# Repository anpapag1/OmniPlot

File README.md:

# OmniPlot

OmniPlot is an ESP-based controller sketch for a 3-wheel omnidirectional plotting robot. The main sketch is `OmniPlot.ino` and it uses the AccelStepper and MultiStepper libraries to drive three stepper motors.

This repository also contains PCB/board files under the `OmniPlot-PCB/` folder.

## Quick summary

- Libraries to download: 
  - AccelStepper.h  `for steppers`
  - ESP32Servo.h  `for pen servo`
  - Adafruit_SSD1306.h `for display`

- Pinout:
  - Stepper1 (Back left) (`step = 35`, `dir  = 34`, `en  = 26`)
  - Stepper2 (front) (`step = 14`, `dir  = 12`, `en  = 27`)
  - Stepper3 (Back right) (`step = 25`, `dir  = 33`, `en  = 32`)
  - Pen_Servo (`servo_Pin = 23`)
  - Encoder (`A = 19`, `B = 18`, `btn = 5`)
  - Oled 
    - `SCREEN_WIDTH 128`
    - `SCREEN_HEIGHT 32`
    - `OLED_RESET -1 `
    - `SCREEN_ADDRESS 0x3C`

## Functions and behavior

This section documents the important functions in `OmniPlot.ino` and what each does.

- `GnR(int speed, int steps1, int steps2, int steps3)`
  - Sets `setMaxSpeed(speed)` for each stepper (units: steps per second for AccelStepper).
  - Writes the requested target positions into a `long gotoposition[3]` array.
  - Calls `steppersControl.moveTo(gotoposition);` followed by `steppersControl.runSpeedToPosition();` — this blocks until all steppers reach their target positions.
  - Waits 1 second, then commands all motors to return to position zero and waits again.

- `omniTest()`
  - A simple test routine that calls `GnR(...)` with several sets of speeds and step targets to demonstrate movement patterns. The calls look like:
    - `GnR(1000, 1000, -1000, 0);`
    - `GnR(2000, 0, 1000, -1000);`
    - and so on.
  - These sequences are examples — change or expand them to drive your robot.

- `spin(int steps)`
  - Example helper that sets all motors to a target (int steps) and back to zero. Also uses `runSpeedToPosition()` so it blocks until complete.

## Rotary Encoder with Interrupts

To read a rotary encoder efficiently using hardware interrupts on ESP32, use the following code pattern:

```cpp
// Encoder pin definitions
const int encoderPinA = 19;  // CLK
const int encoderPinB = 18;  // DT
const int encoderBtn = 5;    // SW (button)

volatile long encoderPosition = 0;
volatile bool buttonPressed = false;

// Interrupt service routine for encoder
void IRAM_ATTR encoderISR() {
  int stateB = digitalRead(encoderPinB);
  if (stateB == HIGH) {
    encoderPosition++;  // Clockwise
  } else {
    encoderPosition--;  // Counter-clockwise
  }
}

// Interrupt service routine for button
void IRAM_ATTR buttonISR() {
  buttonPressed = true;
}

void setup() {
  // Configure encoder pins
  pinMode(encoderPinA, INPUT_PULLUP);
  pinMode(encoderPinB, INPUT_PULLUP);
  pinMode(encoderBtn, INPUT_PULLUP);
  
  // Attach interrupts (trigger on FALLING edge)
  attachInterrupt(digitalPinToInterrupt(encoderPinA), encoderISR, FALLING);
  attachInterrupt(digitalPinToInterrupt(encoderBtn), buttonISR, FALLING);
}

void loop() {
  // Read encoder position (interrupt updates it automatically)
  static long lastPosition = 0;
  if (encoderPosition != lastPosition) {
    Serial.print("Encoder: ");
    Serial.println(encoderPosition);
    lastPosition = encoderPosition;
  }
  
  // Check button press
  if (buttonPressed) {
    Serial.println("Button pressed!");
    buttonPressed = false;  // Reset flag
    delay(200);  // Simple debounce
  }
}
```

**Key points:**
- Use `IRAM_ATTR` for interrupt functions to place them in RAM for faster execution
- Use `volatile` for variables shared between interrupts and main code
- GPIO 19 and 18 support interrupts and are safe for encoder use
- The encoder position updates automatically in the background via interrupts

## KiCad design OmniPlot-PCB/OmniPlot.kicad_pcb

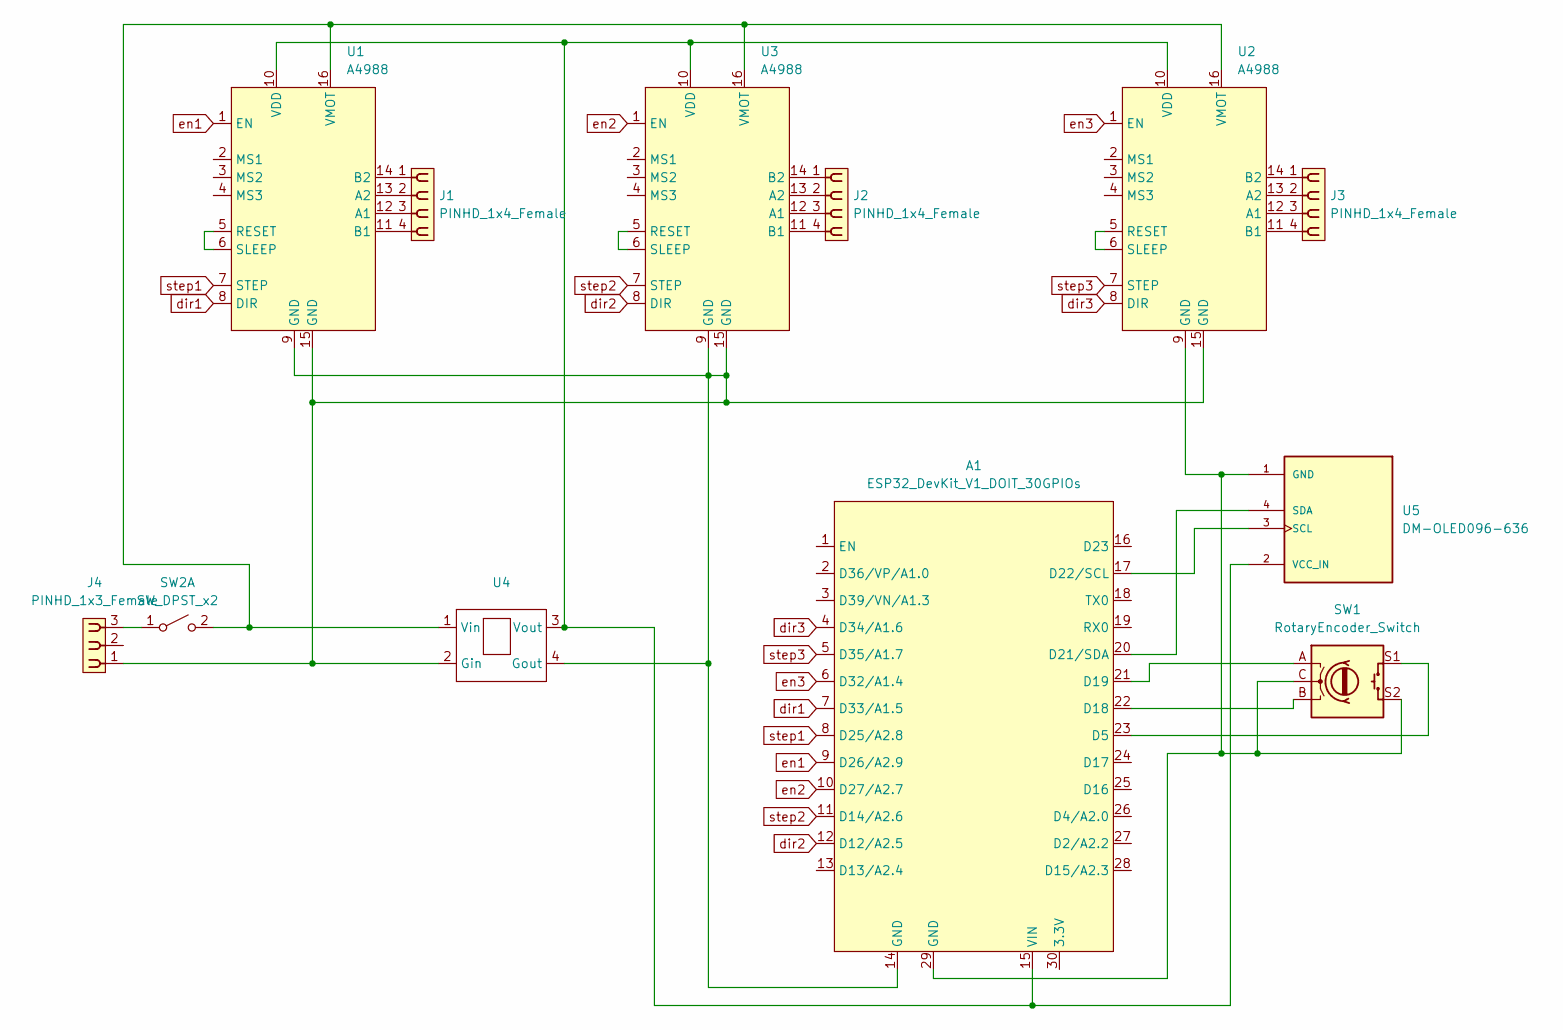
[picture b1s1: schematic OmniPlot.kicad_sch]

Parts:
A1: ESP32_DevKit_V1_DOIT_30GPIOs; DOIT_ESP32_DEVKIT_30Pins
J1, J2, J3: PINHD_1x4_Female; PinSocket_1x04_P2.54mm_Vertical
J4: PINHD_1x3_Female; PinSocket_1x03_P2.54mm_Vertical
SW1: RotaryEncoder_Switch; RotaryEncoder_Alps_EC11E-Switch_Vertical_H20mm
SW2: SW_DPST_x2; PinSocket_1x03_P2.54mm_Vertical
U1, U2, U3: A4988; A4988_Breakout
U4: 12v to 5v
U5: DM-OLED096-636; MODULE_DM-OLED096-636; PARTREV 2018-09-10

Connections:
unnamed: A1.23 (D5), SW1.S1
unnamed: A1.22 (D18), SW1.B
unnamed: A1.21 (D19), SW1.A
unnamed: A1.20 (D21/SDA), U5.4 (SDA)
unnamed: A1.17 (D22/SCL), U5.3 (SCL)
unnamed: A1.15 (VIN), U1.10 (VDD), U2.10 (VDD), U3.10 (VDD), U4.3 (Vout), U5.2 (VCC_IN)
unnamed: J4.3, SW2.1 (A)
unnamed: SW2.2 (B), U1.16 (VMOT), U2.16 (VMOT), U3.16 (VMOT), U4.1 (Vin)
unnamed: J1.3, U1.12 (A1)
unnamed: J1.2, U1.13 (A2)
unnamed: J1.4, U1.11 (B1)
unnamed: J1.1, U1.14 (B2)
unnamed: U1.5 (RESET), U1.6 (SLEEP)
unnamed: J3.3, U2.12 (A1)
unnamed: J3.2, U2.13 (A2)
unnamed: J3.4, U2.11 (B1)
unnamed: J3.1, U2.14 (B2)
unnamed: U2.5 (RESET), U2.6 (SLEEP)
unnamed: J2.3, U3.12 (A1)
unnamed: J2.2, U3.13 (A2)
unnamed: J2.4, U3.11 (B1)
unnamed: J2.1, U3.14 (B2)
unnamed: U3.5 (RESET), U3.6 (SLEEP)
unnamed: A1.14 (GND), J4.1, U1.9 (GND), U1.15 (GND), U2.15 (GND), U3.9 (GND), U3.15 (GND), U4.2 (Gin), U4.4 (Gout)
unnamed: A1.29 (GND), SW1.C, SW1.S2, U2.9 (GND), U5.1 (GND)
dir1: A1.7 (D33/A1.5), U1.8 (DIR)
dir2: A1.12 (D12/A2.5), U3.8 (DIR)
dir3: A1.4 (D34/A1.6), U2.8 (DIR)
en1: A1.9 (D26/A2.9), U1.1 (EN)
en2: A1.10 (D27/A2.7), U3.1 (EN)
en3: A1.6 (D32/A1.4), U2.1 (EN)
step1: A1.8 (D25/A2.8), U1.7 (STEP)
step2: A1.11 (D14/A2.6), U3.7 (STEP)
step3: A1.5 (D35/A1.7), U2.7 (STEP)

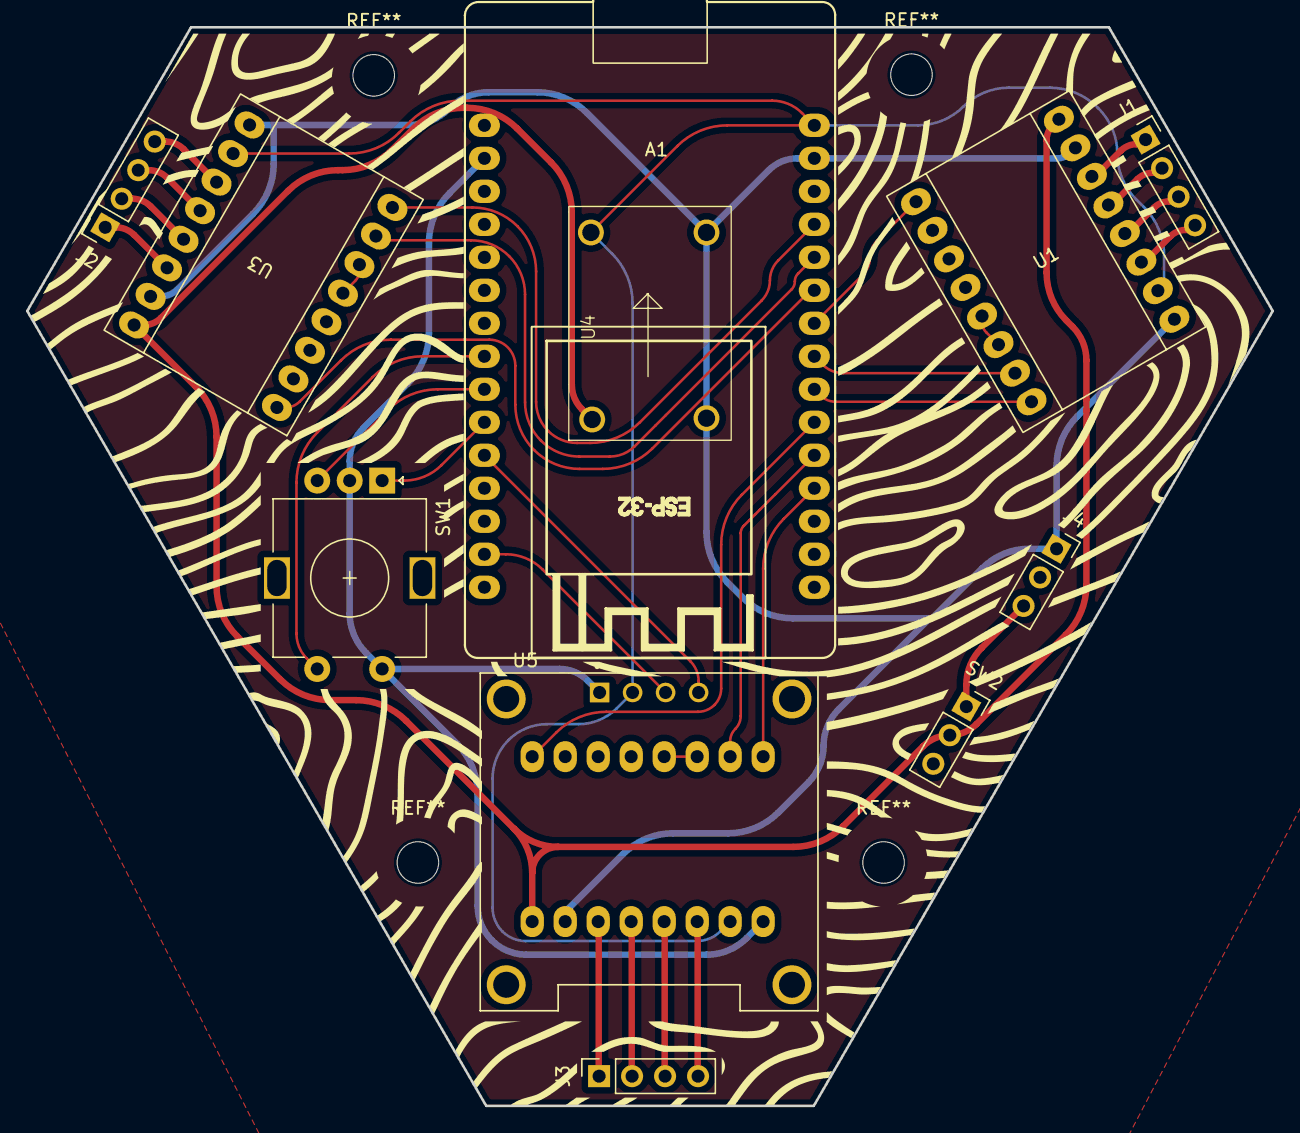
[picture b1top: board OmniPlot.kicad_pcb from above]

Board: 2 copper layers, 95.9 x 83.0 mm, 12 parts (1 on the bottom side), 34 nets.

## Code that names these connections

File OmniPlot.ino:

#include <AccelStepper.h>
#include <MultiStepper.h>

// Pin definitions for Motor 1 (Back-Left)
const int step1 = 16;
const int dir1 = 17;
const int en1 = 26;

// Pin definitions for Motor 2 (Front)
const int step2 = 14;
const int dir2 = 12;
const int en2 = 27;

// Pin definitions for Motor 3 (Back-Right)
const int step3 = 25;
const int dir3 = 33;
const int en3 = 32;

// Define the stepper motor and the pins that is connected to
AccelStepper stepper1(1, step1, dir1); // (Typeof driver: with 2 pins, STEP, DIR)
AccelStepper stepper2(1, step2, dir2);
AccelStepper stepper3(1, step3, dir3);

MultiStepper steppersControl;  // Create instance of MultiStepper

long gotoposition[3]; // An array to store the target positions for each stepper motor

void setup() {
  // Set enable pins as outputs and enable the drivers (LOW = enabled)
  pinMode(en1, OUTPUT);
  pinMode(en2, OUTPUT);
  pinMode(en3, OUTPUT);
  digitalWrite(en1, LOW);
  digitalWrite(en2, LOW);
  digitalWrite(en3, LOW);

  // Adding the 3 steppers to the steppersControl instance for multi stepper control
  steppersControl.addStepper(stepper1);
  steppersControl.addStepper(stepper2);
  steppersControl.addStepper(stepper3);
}

void loop() {
  // spin(1000); // Example spin movement
  omniTest();

}

void omniTest() {
  // Example movements to test omni-directional movement
  GnR(1000, 1000, -1000, 0); // speed, steps for motor1, motor2, motor3
  GnR(2000, 0, 1000, -1000);
  GnR(800, -1000, 0, 1000);
  GnR(1000, 1500, 1500, 1500);
  GnR(700, -500, -500, -500);
}

// Go to specified positions and return to zero 
void GnR(int speed, int steps1, int steps2, int steps3) {
  stepper1.setMaxSpeed(speed); // Set maximum speed value for the stepper
  stepper2.setMaxSpeed(speed);
  stepper3.setMaxSpeed(speed);

  // Store the target positions in the "gotopostion" array
  gotoposition[0] = steps1;  
  gotoposition[1] = steps2;
  gotoposition[2] = steps3;

  steppersControl.moveTo(gotoposition); // Calculates the required speed for all motors
  steppersControl.runSpeedToPosition(); // Blocks until all steppers are in position

  delay(1000);

  gotoposition[0] = 0;
  gotoposition[1] = 0;
  gotoposition[2] = 0;

  steppersControl.moveTo(gotoposition);
  steppersControl.runSpeedToPosition();

  delay(1000);

}

void spin(int steps) {
  stepper1.setMaxSpeed(1000); // Set maximum speed value for the stepper
  stepper2.setMaxSpeed(1000);
  stepper3.setMaxSpeed(1000);

  // Store the target positions in the "gotopostion" array
  gotoposition[0] = steps;  // 800 steps - full rotation with quater-step resolution
  gotoposition[1] = steps;
  gotoposition[2] = steps;

  steppersControl.moveTo(gotoposition); // Calculates the required speed for all motors
  steppersControl.runSpeedToPosition(); // Blocks until all steppers are in position

  delay(1000);

  gotoposition[0] = 0;
  gotoposition[1] = 0;
  gotoposition[2] = 0;

  steppersControl.moveTo(gotoposition);
  steppersControl.runSpeedToPosition();

  delay(1000);

}

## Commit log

2025-11-07 Refactor motor speed settings and update README documentation
2025-11-13 Update motor pin definitions and enhance README documentation
